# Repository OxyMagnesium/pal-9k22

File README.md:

# Avionics PCB Design

This is the PSPHA Avionics PCB design. It uses an ATtiny MCU, Barometer, IMU to measure flight data and record it to a flash memory chip.

## Pin Map

| Port | Pin 1 | Pin 2            | Pin 3        | Pin 4        | Pin 5        | Pin 6        |
| ---- | ----- | ---------------- | ------------ | ------------ | ------------ | ------------ |
| J1   | GND   | SCLK             | MISO         | MOSI         |              |              |
| J2   | GND   | PA7              |              |              |              |              |
| J3   | GND   | Vin (5 V to 9 V) | Recovery 2 + | Recovery 1 + | Recovery 2 - | Recovery 1 - |
| J4   | GND   | TOSC1            | TOSC2        |              |              |              |
| J5   | GND   | UPDI             |              |              |              |              |
| J6   | GND   | GND              | GND          | 3.3 V        |              |              |

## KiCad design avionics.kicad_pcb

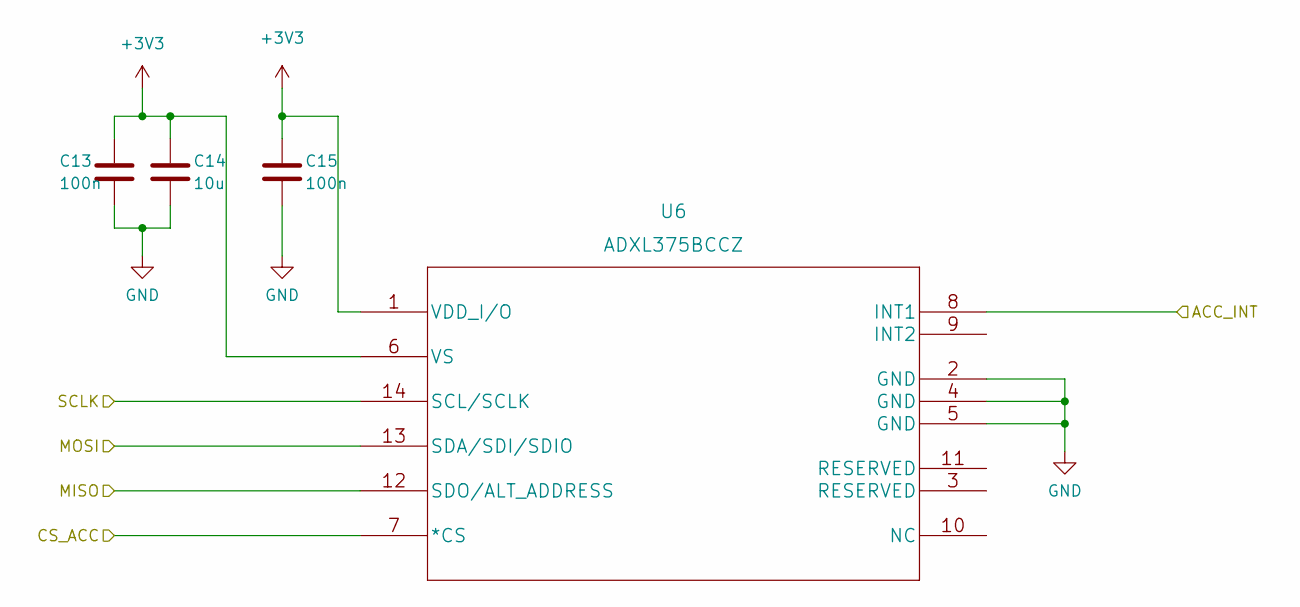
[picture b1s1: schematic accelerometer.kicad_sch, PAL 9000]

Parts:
C13, C15: 100n; C_0603_1608Metric
C14: 10u; C_0603_1608Metric
U6: ADXL375BCCZ; LGA-14_3x5mm_P0.8mm_LayoutBorder1x6y

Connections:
+3V3: C13.1, C14.1, C15.1, U6.1 (VDD_I/O), U6.6 (VS); also elsewhere on the board
/Accelerometer/ACC_INT: U6.8 (INT1); also elsewhere on the board
/Accelerometer/CS_ACC: U6.7 (*CS); also elsewhere on the board
/Accelerometer/MISO: U6.12 (SDO/ALT_ADDRESS); also elsewhere on the board
/Accelerometer/MOSI: U6.13 (SDA/SDI/SDIO); also elsewhere on the board
/Accelerometer/SCLK: U6.14 (SCL/SCLK); also elsewhere on the board
GND: C13.2, C14.2, C15.2, U6.2 (GND), U6.4 (GND), U6.5 (GND); also elsewhere on the board

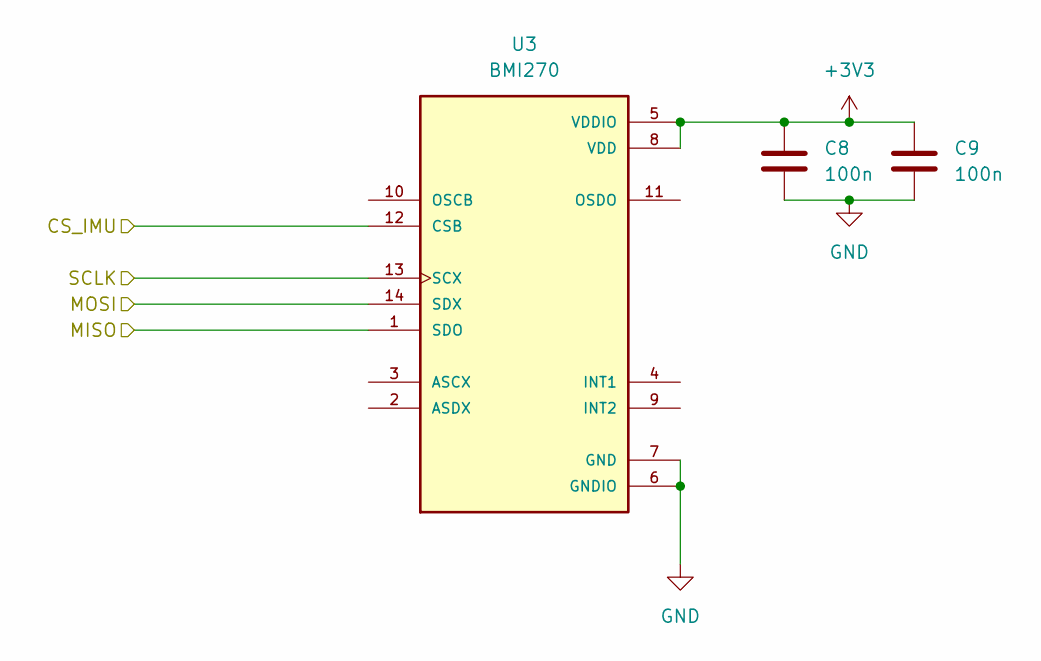
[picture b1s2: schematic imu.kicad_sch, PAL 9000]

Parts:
C8, C9: 100n; C_0603_1608Metric
U3: BMI270; XDCR_BMI270

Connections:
+3V3: C8.1, C9.1, U3.5 (VDDIO), U3.8 (VDD); also elsewhere on the board
/Accelerometer/MISO: U3.1 (SDO); also elsewhere on the board
/Accelerometer/MOSI: U3.14 (SDX); also elsewhere on the board
/Accelerometer/SCLK: U3.13 (SCX); also elsewhere on the board
/IMU/CS_IMU: U3.12 (CSB); also elsewhere on the board
GND: C8.2, C9.2, U3.6 (GNDIO), U3.7 (GND); also elsewhere on the board

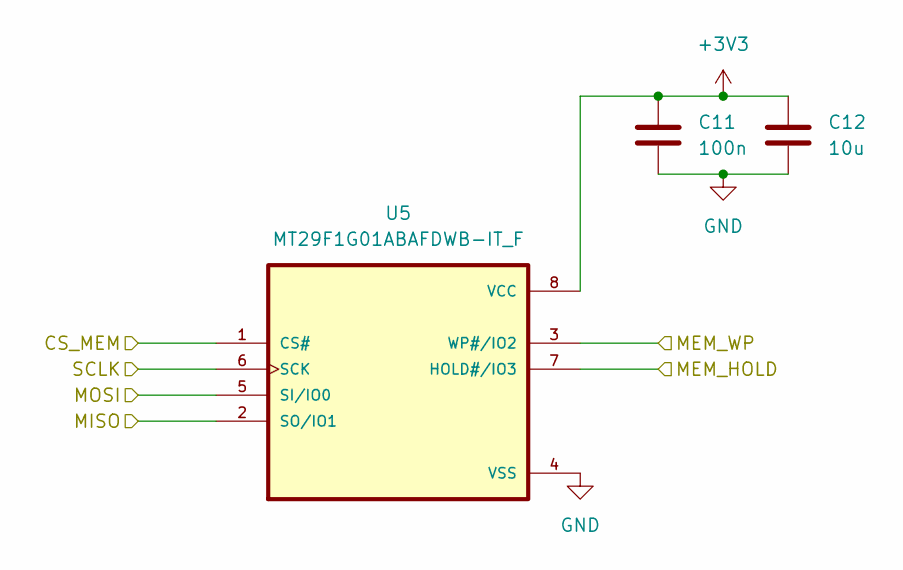
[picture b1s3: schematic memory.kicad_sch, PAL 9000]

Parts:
C11: 100n; C_0603_1608Metric
C12: 10u; C_0603_1608Metric
U5: MT29F1G01ABAFDWB-IT_F; SON127P600X800X65-8N; PARTREV LTR

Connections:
+3V3: C11.1, C12.1, U5.8 (VCC); also elsewhere on the board
/Accelerometer/MISO: U5.2 (SO/IO1); also elsewhere on the board
/Accelerometer/MOSI: U5.5 (SI/IO0); also elsewhere on the board
/Accelerometer/SCLK: U5.6 (SCK); also elsewhere on the board
/MCU/CS_MEM: U5.1 (CS#); also elsewhere on the board
/MCU/MEM_HOLD: U5.7 (HOLD#/IO3); also elsewhere on the board
/MCU/MEM_WP: U5.3 (WP#/IO2); also elsewhere on the board
GND: C11.2, C12.2, U5.4 (VSS); also elsewhere on the board

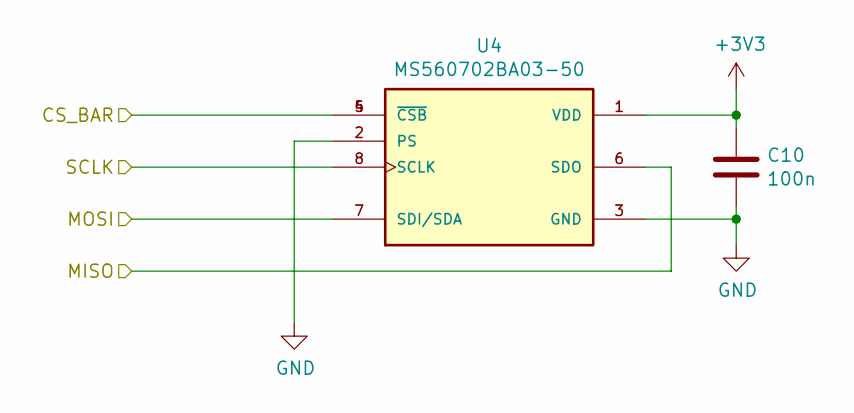
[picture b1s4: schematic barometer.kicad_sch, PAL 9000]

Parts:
C10: 100n; C_0603_1608Metric
U4: MS560702BA03-50; SON125P300X500X100-8N

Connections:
+3V3: C10.1, U4.1 (VDD); also elsewhere on the board
/Accelerometer/MISO: U4.6 (SDO); also elsewhere on the board
/Accelerometer/MOSI: U4.7 (SDI/SDA); also elsewhere on the board
/Accelerometer/SCLK: U4.8 (SCLK); also elsewhere on the board
/Barometer/CS_BAR: U4.4 (~CSB), U4.5 (~CSB); also elsewhere on the board
GND: C10.2, U4.2 (PS), U4.3 (GND); also elsewhere on the board

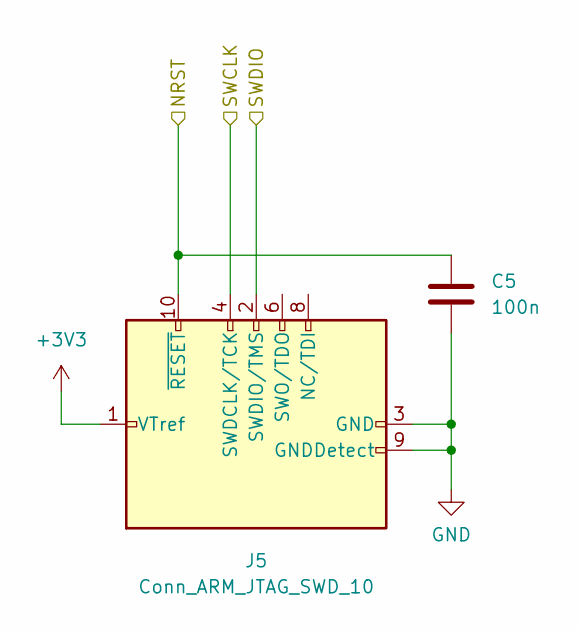
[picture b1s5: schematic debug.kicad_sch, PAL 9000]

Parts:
C5: 100n; C_0603_1608Metric
J5: Conn_ARM_JTAG_SWD_10; ARM-JTAG-10-SWD-IDC

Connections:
+3V3: J5.1 (VTref); also elsewhere on the board
/Debug/NRST: C5.1, J5.10 (~RESET); also elsewhere on the board
/Debug/SWCLK: J5.4 (SWDCLK/TCK); also elsewhere on the board
/Debug/SWDIO: J5.2 (SWDIO/TMS); also elsewhere on the board
GND: C5.2, J5.3 (GND), J5.5 (GND), J5.9 (GNDDetect); also elsewhere on the board

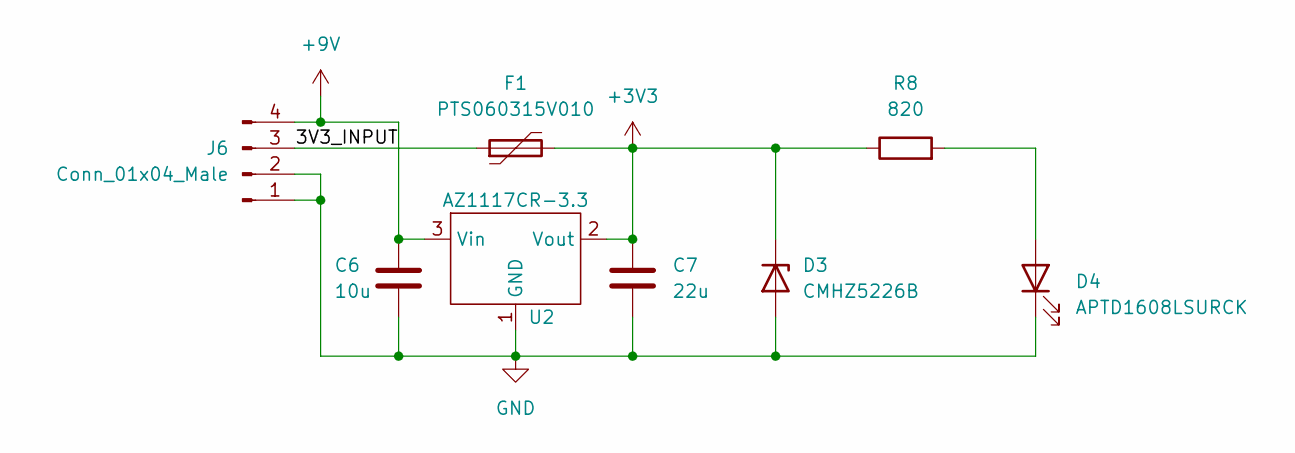
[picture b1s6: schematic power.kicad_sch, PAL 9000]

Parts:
C6: 10u; C_0603_1608Metric
C7: 22u; C_0603_1608Metric
D3: CMHZ5226B; D_SOD-123
D4: APTD1608LSURCK; LED_0603_1608Metric
F1: PTS060315V010; Fuse_0603_1608Metric
J6: Conn_01x04_Male; PinHeader_1x04_P2.54mm_Vertical
R8: 820; R_0603_1608Metric
U2: AZ1117CR-3.3; SOT-89-3

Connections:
+3V3: C7.1, D3.1 (K), F1.2, R8.1, U2.2 (Vout); also elsewhere on the board
+9V: C6.1, J6.4, U2.3 (Vin); also elsewhere on the board
/Power/3V3_INPUT: F1.1, J6.3
GND: C6.2, C7.2, D3.2 (A), D4.1 (K), J6.1, J6.2, U2.1 (GND); also elsewhere on the board
unnamed: D4.2 (A), R8.2

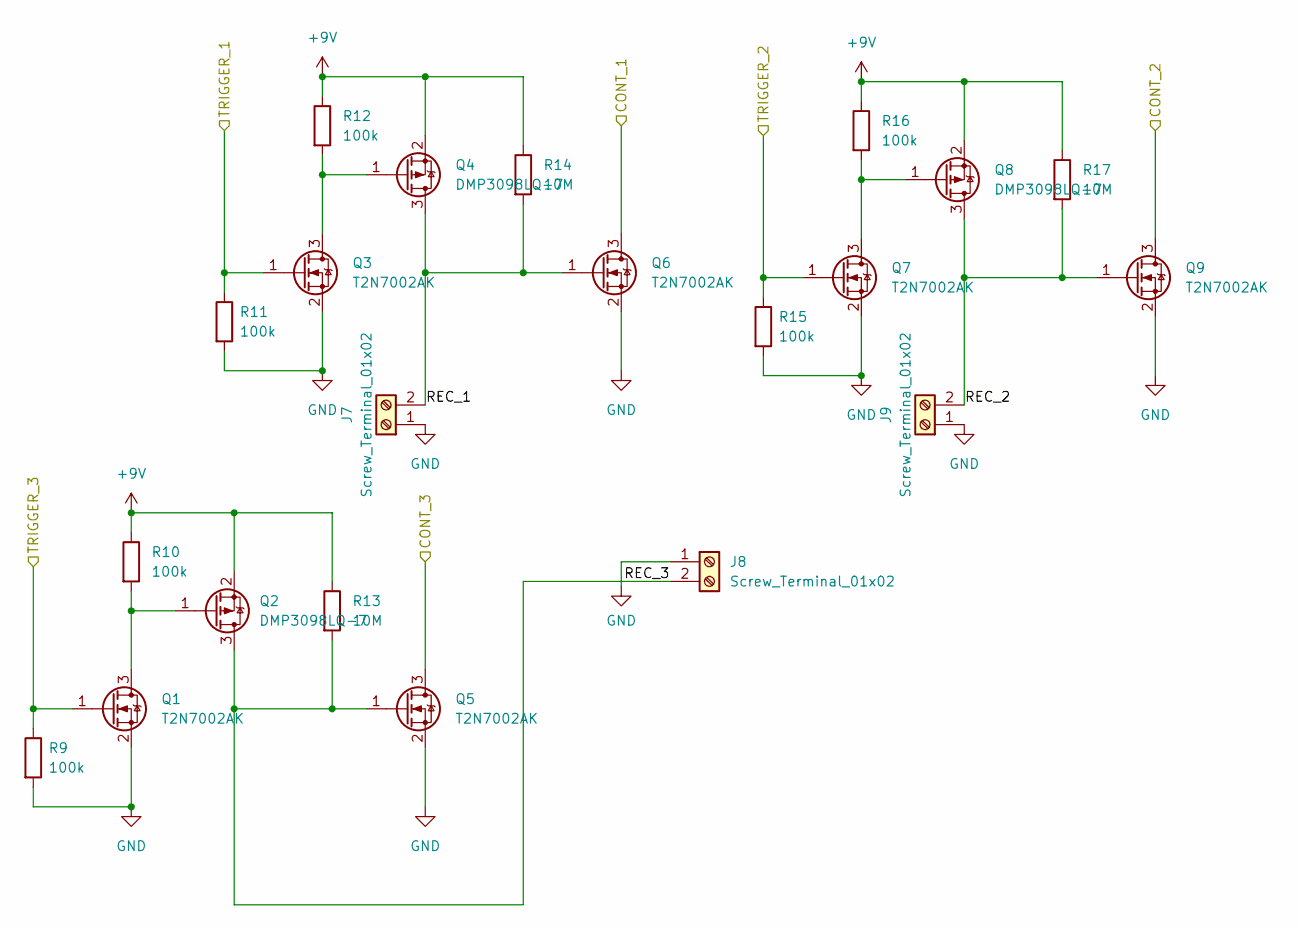
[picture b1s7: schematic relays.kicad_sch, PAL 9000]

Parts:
J7, J8, J9: Screw_Terminal_01x02; PinHeader_1x02_P2.54mm_Vertical
Q1, Q3, Q5, Q6, Q7, Q9: T2N7002AK; SOT-23
Q2, Q4, Q8: DMP3098LQ-7; SOT-23
R9, R10, R11, R12, R15, R16: 100k; R_0603_1608Metric
R13, R14, R17: 10M; R_0603_1608Metric

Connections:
+9V: Q2.2 (S), Q4.2 (S), Q8.2 (S), R10.1, R12.1, R13.1, R14.1, R16.1, R17.1; also elsewhere on the board
/MCU/CONT_1: Q6.3 (D); also elsewhere on the board
/MCU/CONT_2: Q9.3 (D); also elsewhere on the board
/MCU/CONT_3: Q5.3 (D); also elsewhere on the board
/MCU/TRIGGER_1: Q3.1 (G), R11.1; also elsewhere on the board
/MCU/TRIGGER_2: Q7.1 (G), R15.1; also elsewhere on the board
/MCU/TRIGGER_3: Q1.1 (G), R9.1; also elsewhere on the board
/Relays/REC_1: J7.2, Q4.3 (D), Q6.1 (G), R14.2
/Relays/REC_2: J9.2, Q8.3 (D), Q9.1 (G), R17.2
/Relays/REC_3: J8.2, Q2.3 (D), Q5.1 (G), R13.2
GND: J7.1, J8.1, J9.1, Q1.2 (S), Q3.2 (S), Q5.2 (S), Q6.2 (S), Q7.2 (S), Q9.2 (S), R9.2, R11.2, R15.2; also elsewhere on the board
unnamed: Q1.3 (D), Q2.1 (G), R10.2
unnamed: Q3.3 (D), Q4.1 (G), R12.2
unnamed: Q7.3 (D), Q8.1 (G), R16.2

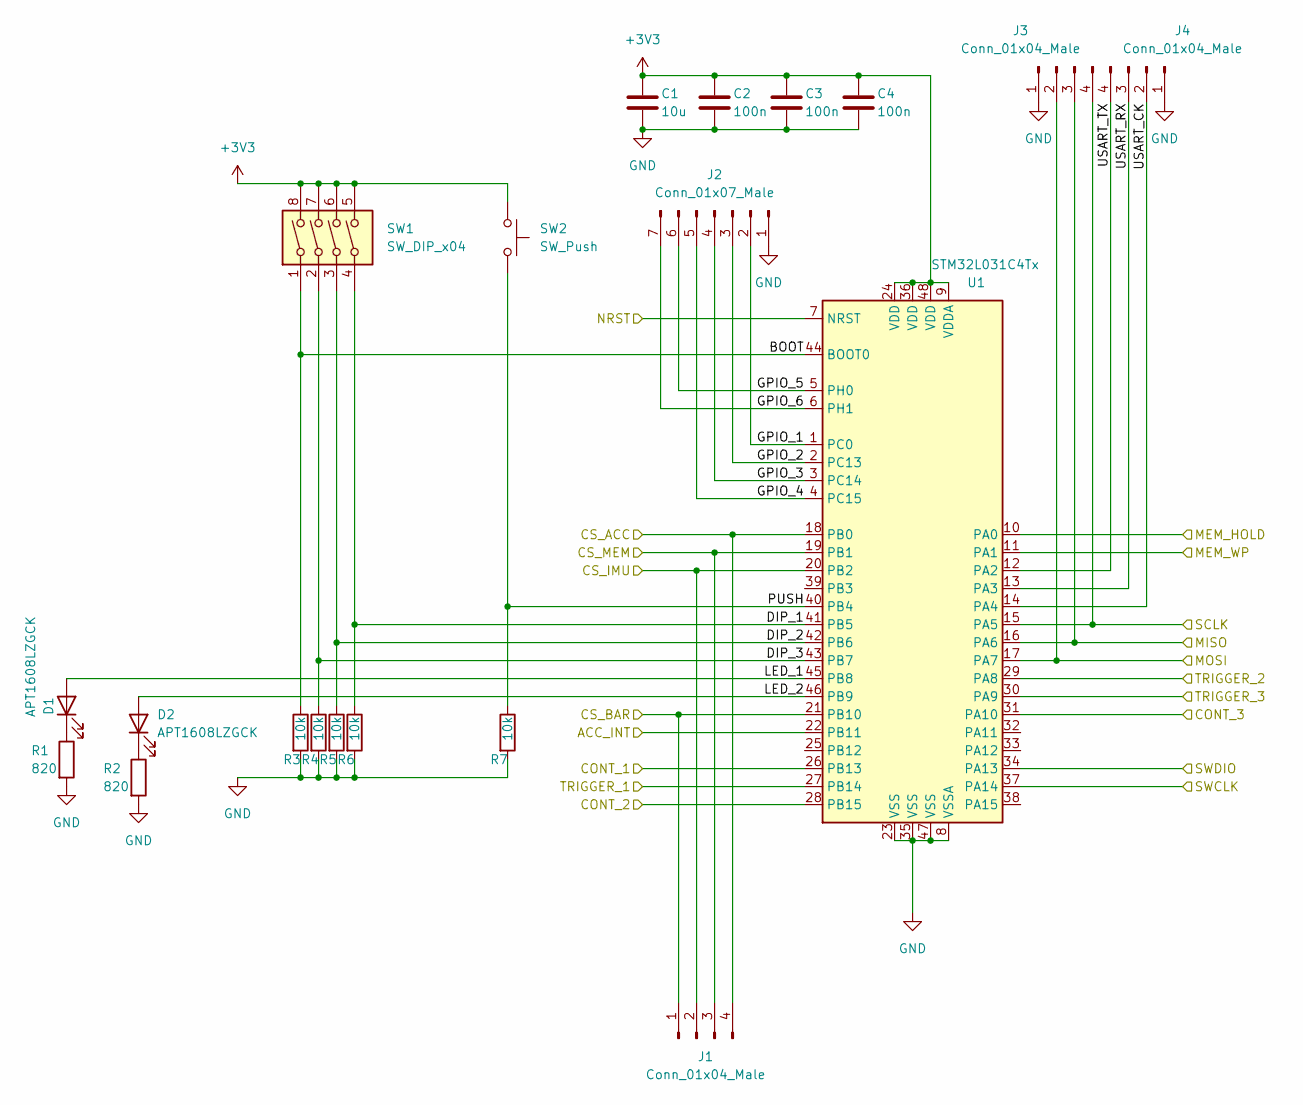
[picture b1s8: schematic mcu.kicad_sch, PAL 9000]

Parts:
C1: 10u; C_0603_1608Metric
C2, C3, C4: 100n; C_0603_1608Metric
D1, D2: APT1608LZGCK; LED_0603_1608Metric
J1, J3, J4: Conn_01x04_Male; PinHeader_1x04_P2.54mm_Vertical
J2: Conn_01x07_Male; PinHeader_1x07_P2.54mm_Vertical
R1, R2: 820; R_0603_1608Metric
R3, R4, R5, R6, R7: 10k; R_0603_1608Metric
SW1: SW_DIP_x04; SW_DIP_SPSTx04_Slide_Omron_A6S-410x_W8.9mm_P2.54mm
SW2: SW_Push; SW_Push_1P1T_NO_CK_KSC7xxJ
U1: STM32L031C4Tx; LQFP-48_7x7mm_P0.5mm

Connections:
+3V3: C1.1, C2.1, C3.1, C4.1, SW1.5, SW1.6, SW1.7, SW1.8, SW2.1, U1.9 (VDDA), U1.24 (VDD), U1.36 (VDD), U1.48 (VDD); also elsewhere on the board
/Accelerometer/ACC_INT: U1.22 (PB11); also elsewhere on the board
/Accelerometer/CS_ACC: J1.4, U1.18 (PB0); also elsewhere on the board
/Accelerometer/MISO: J3.3, U1.16 (PA6); also elsewhere on the board
/Accelerometer/MOSI: J3.2, U1.17 (PA7); also elsewhere on the board
/Accelerometer/SCLK: J3.4, U1.15 (PA5); also elsewhere on the board
/Barometer/CS_BAR: J1.1, U1.21 (PB10); also elsewhere on the board
/Debug/NRST: U1.7 (NRST); also elsewhere on the board
/Debug/SWCLK: U1.37 (PA14); also elsewhere on the board
/Debug/SWDIO: U1.34 (PA13); also elsewhere on the board
/IMU/CS_IMU: J1.2, U1.20 (PB2); also elsewhere on the board
/MCU/BOOT: R3.1, SW1.1, U1.44 (BOOT0)
/MCU/CONT_1: U1.26 (PB13); also elsewhere on the board
/MCU/CONT_2: U1.28 (PB15); also elsewhere on the board
/MCU/CONT_3: U1.31 (PA10); also elsewhere on the board
/MCU/CS_MEM: J1.3, U1.19 (PB1); also elsewhere on the board
/MCU/DIP_1: R6.1, SW1.4, U1.41 (PB5)
/MCU/DIP_2: R5.1, SW1.3, U1.42 (PB6)
/MCU/DIP_3: R4.1, SW1.2, U1.43 (PB7)
/MCU/GPIO_1: J2.2, U1.1 (PC0)
/MCU/GPIO_2: J2.3, U1.2 (PC13)
/MCU/GPIO_3: J2.4, U1.3 (PC14)
/MCU/GPIO_4: J2.5, U1.4 (PC15)
/MCU/GPIO_5: J2.6, U1.5 (PH0)
/MCU/GPIO_6: J2.7, U1.6 (PH1)
/MCU/LED_1: D1.2 (A), U1.45 (PB8)
/MCU/LED_2: D2.2 (A), U1.46 (PB9)
/MCU/MEM_HOLD: U1.10 (PA0); also elsewhere on the board
/MCU/MEM_WP: U1.11 (PA1); also elsewhere on the board
/MCU/PUSH: R7.1, SW2.2, U1.40 (PB4)
/MCU/TRIGGER_1: U1.27 (PB14); also elsewhere on the board
/MCU/TRIGGER_2: U1.29 (PA8); also elsewhere on the board
/MCU/TRIGGER_3: U1.30 (PA9); also elsewhere on the board
/MCU/USART_CK: J4.2, U1.14 (PA4)
/MCU/USART_RX: J4.3, U1.13 (PA3)
/MCU/USART_TX: J4.4, U1.12 (PA2)
GND: C1.2, C2.2, C3.2, C4.2, J2.1, J3.1, J4.1, R1.2, R2.2, R3.2, R4.2, R5.2, R6.2, R7.2, U1.8 (VSSA), U1.23 (VSS), U1.35 (VSS), U1.47 (VSS); also elsewhere on the board
unnamed: D1.1 (K), R1.1
unnamed: D2.1 (K), R2.1

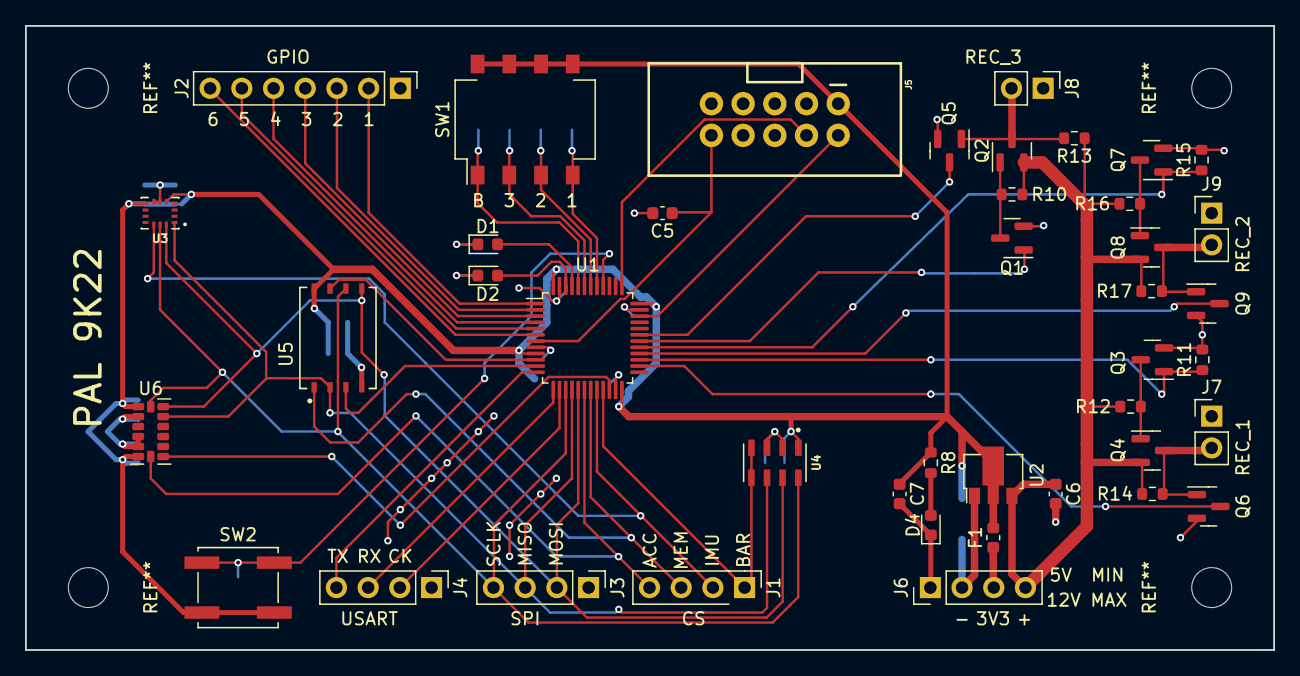
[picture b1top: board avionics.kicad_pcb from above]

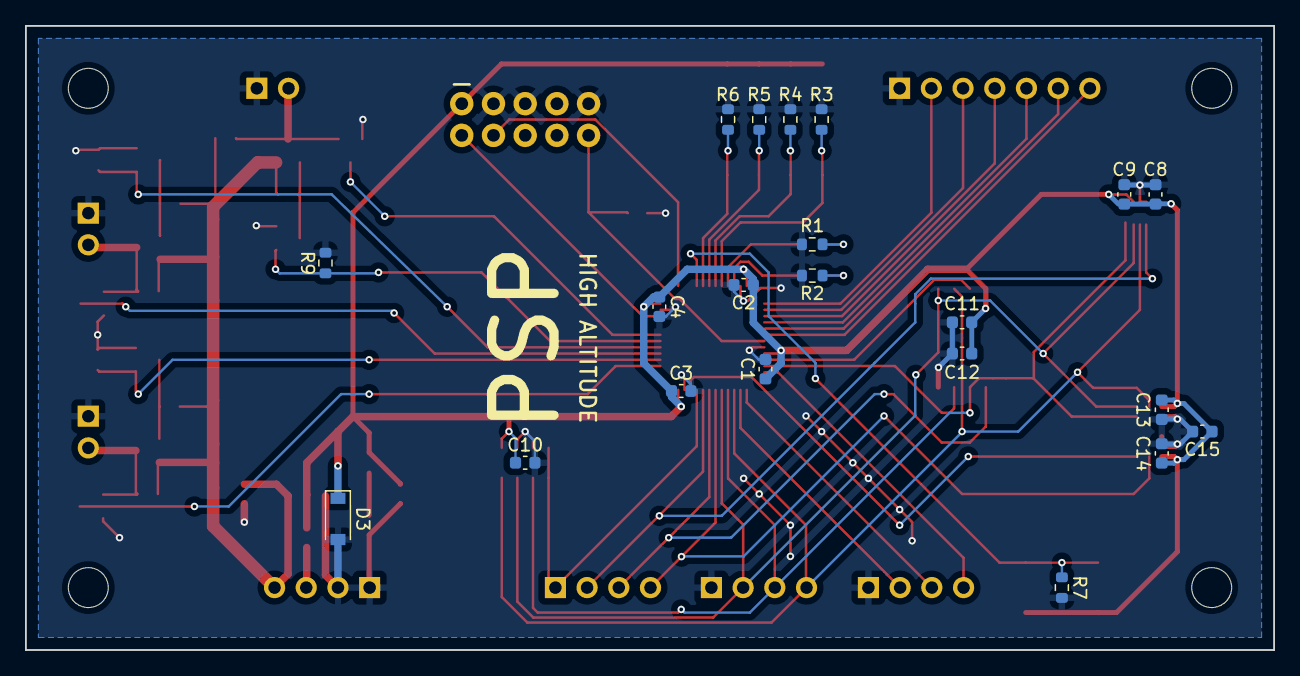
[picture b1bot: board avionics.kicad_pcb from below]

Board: 2 copper layers, 100.0 x 50.0 mm, 63 parts (21 on the bottom side), 48 nets.
